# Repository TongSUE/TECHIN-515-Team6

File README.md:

# AuraSync — Context-Aware Scent Diffuser

**AuraSync** automatically detects bathroom context (shower, odor, presence) via sensor fusion and triggers a fragrance diffuser at the right moment — no manual input required.

**Devlog:** [tongsue.github.io/TECHIN-515-Team6](https://tongsue.github.io/TECHIN-515-Team6/)  
**Course:** TECHIN 515 Hardware-Software Lab II, UW, Spring 2026  
**Team:** Yutong Luo (@TongSUE) · Lucia Shen (@xtshen777)

---

## Hardware

| Component | Role |
|---|---|
| Seeed XIAO ESP32-S3 | MCU — dual-core, 8 MB PSRAM, native I2S |
| Adafruit SPH0645LM4H | I2S MEMS microphone — voice recognition |
| HC-SR501 PIR | Presence detection — triggers actuation |
| Adafruit BME680 | Temp / humidity / pressure / VOC (I2C 0x77) |
| Ultrasonic atomizer + 2N2222 NPN | Fragrance mist actuation |
| MT3608 boost converter + 3.7 V LiPo | Power supply |

### Pin Assignments

| Function | Arduino Pin | GPIO |
|---|---|---|
| I2C SDA (BME680) | D4 | 5 |
| I2C SCL (BME680) | D5 | 6 |
| I2S BCLK (SPH0645) | D8 | 7 |
| I2S LRCLK (SPH0645) | D9 | 8 |
| I2S DOUT (SPH0645) | D10 | 9 |
| PIR signal (HC-SR501) | — | 4 |
| Atomizer MOSFET gate | — | 5 |
| Status LED | D0 | 21 |

> SPH0645: SEL pin → GND (left channel). Data in bits [31:14] of 32-bit I2S frame.  
> BME680: use `Wire.begin()` with no arguments — the framework maps D4/D5 by default.

---

## Repository Layout

```
Web/                          ← git root (this repo)
├── Code/
│   ├── AuraSync/             ← main firmware (two-layer state machine)
│   │   ├── AuraSync.ino
│   │   ├── partitions.csv    ← custom flash layout (app0 3.7 MB + model SPIFFS 4.25 MB)
│   │   └── secrets.h.example ← copy to secrets.h and fill in credentials
│   ├── VoiceTest/            ← ESP-SR voice recognition prototype
│   │   └── voice_monitor.html← Web Serial browser monitor
│   ├── FirebaseTest/         ← VoiceTest + Firebase Realtime Database
│   ├── MicTest/              ← SPH0645 bring-up / VAD test
│   ├── PIRTest/              ← PIR motion-triggered spray controller
│   └── PsramTest/            ← PSRAM validation
├── KiCAD/AuraSync_v1/        ← schematic + PCB layout (KiCAD 9)
├── monitor/
│   ├── voice_monitor.py      ← real-time serial monitor (USB, Streamlit)
│   ├── firebase_dashboard.py ← cloud dashboard (reads Firebase, no USB needed)
│   └── requirements.txt
├── web-devlog/               ← React + Vite devlog site
└── README.md
```

---

## Flashing AuraSync (Main Firmware)

1. Copy `Code/AuraSync/secrets.h.example` → `Code/AuraSync/secrets.h` and fill in your WiFi + Firebase credentials
2. Open `Code/AuraSync/AuraSync.ino` in Arduino IDE
3. **Tools → Board:** Seeed XIAO ESP32-S3
4. **Tools → PSRAM:** OPI PSRAM
5. **Tools → Partition Scheme:** Huge APP (3MB No OTA / 1MB SPIFFS)
6. Run `Code/VoiceTest/flash_model.ps1` **once** to write ESP-SR models to flash
7. Upload `AuraSync.ino`
8. Say **"Aura"** to open the 7-second command window, then **"Spray"** or **"Stop"**; PIR presence for ≥ 3 s also triggers spray

---

## Running the Serial Voice Monitor

Streams live audio level and recognised commands from the ESP32-S3 over USB serial.

**Requirements:** Python 3.9+, ESP32-S3 flashed with `VoiceTest.ino` or `AuraSync.ino`, Arduino IDE serial monitor **closed**.

```bash
cd monitor
pip install -r requirements.txt
streamlit run voice_monitor.py
```

Opens at `http://localhost:8501`. The app auto-detects the COM port — no configuration needed.

---

## Running the Firebase Cloud Dashboard

Reads spray events from Firebase Realtime Database — no USB connection required.

```bash
cd monitor
pip install -r requirements.txt
streamlit run firebase_dashboard.py
```

Opens at `http://localhost:8502`. Supports dark/light mode toggle; auto-refreshes every 5 seconds.

---

## Flashing VoiceTest (Voice Recognition Prototype)

1. Open `Code/VoiceTest/VoiceTest.ino` in Arduino IDE
2. **Tools → Board:** Seeed XIAO ESP32-S3
3. **Tools → PSRAM:** OPI PSRAM
4. **Tools → Partition Scheme:** Huge APP (3MB No OTA / 1MB SPIFFS)
5. Run `Code/VoiceTest/flash_model.ps1` **once** to write ESP-SR models to flash
6. Upload `VoiceTest.ino`
7. Say **"Aura"** to open the 7-second command window, then **"Spray"** or **"Stop"**

---

## Firmware Overview

### `Code/AuraSync/AuraSync.ino` — Main firmware (Week 4+)

Two-layer state machine, non-blocking (`millis()` only, no `delay()` in main loop):

**Layer 1 — System Mode** (PIR-driven presence):
```
MODE_SLEEP  ──PIR detected──▶  MODE_AWAKE
MODE_AWAKE  ──60 s no PIR──▶  MODE_SLEEP
```

**Layer 2 — Spray State** (shared absolute cooldown):
```
SPRAY_IDLE → SPRAY_SPRAYING (5 s) → SPRAY_COOLDOWN (20 s test / 3 min prod) → SPRAY_IDLE
```

Four-priority trigger model: P1 voice/app (bypasses cooldown, works in SLEEP) → P2 extreme VOC < 10 kΩ (works in SLEEP, queues during cooldown) → P3 PIR + VOC inflection (AWAKE + IDLE only).

FreeRTOS dual-core: I2S + ESP-SR on Core 1 at max priority; PIR, state machine, Firebase, BME680 on Core 0. Power saving: `WiFi.setSleep(WIFI_PS_MAX_MODEM)` + Core 0 throttle in SLEEP mode (~30 mA idle from 2000 mAh LiPo ≈ 60–70 h).

### `Code/VoiceTest/VoiceTest.ino` — Voice recognition prototype

ESP-SR AFE + MultiNet v7 on FreeRTOS Core 1. Wake-word state machine:

```
IDLE → (say "Aura") → LISTENING [7 s] → (say "Spray"/"Stop") → IDLE
```

### `Code/FirebaseTest/FirebaseTest.ino` — Voice + Firebase

Extends VoiceTest: SR task (Core 1) → FreeRTOS queue → `loop()` (Core 0) → `Firebase.RTDB.pushJSON()`. Auth via database-secret legacy token; NTP time sync at boot.

---

## Devlog Site

Built with React 19 + Vite. Auto-deployed to GitHub Pages.

```bash
cd web-devlog
npm install
npm run dev       # local preview
npm run build     # production build
```

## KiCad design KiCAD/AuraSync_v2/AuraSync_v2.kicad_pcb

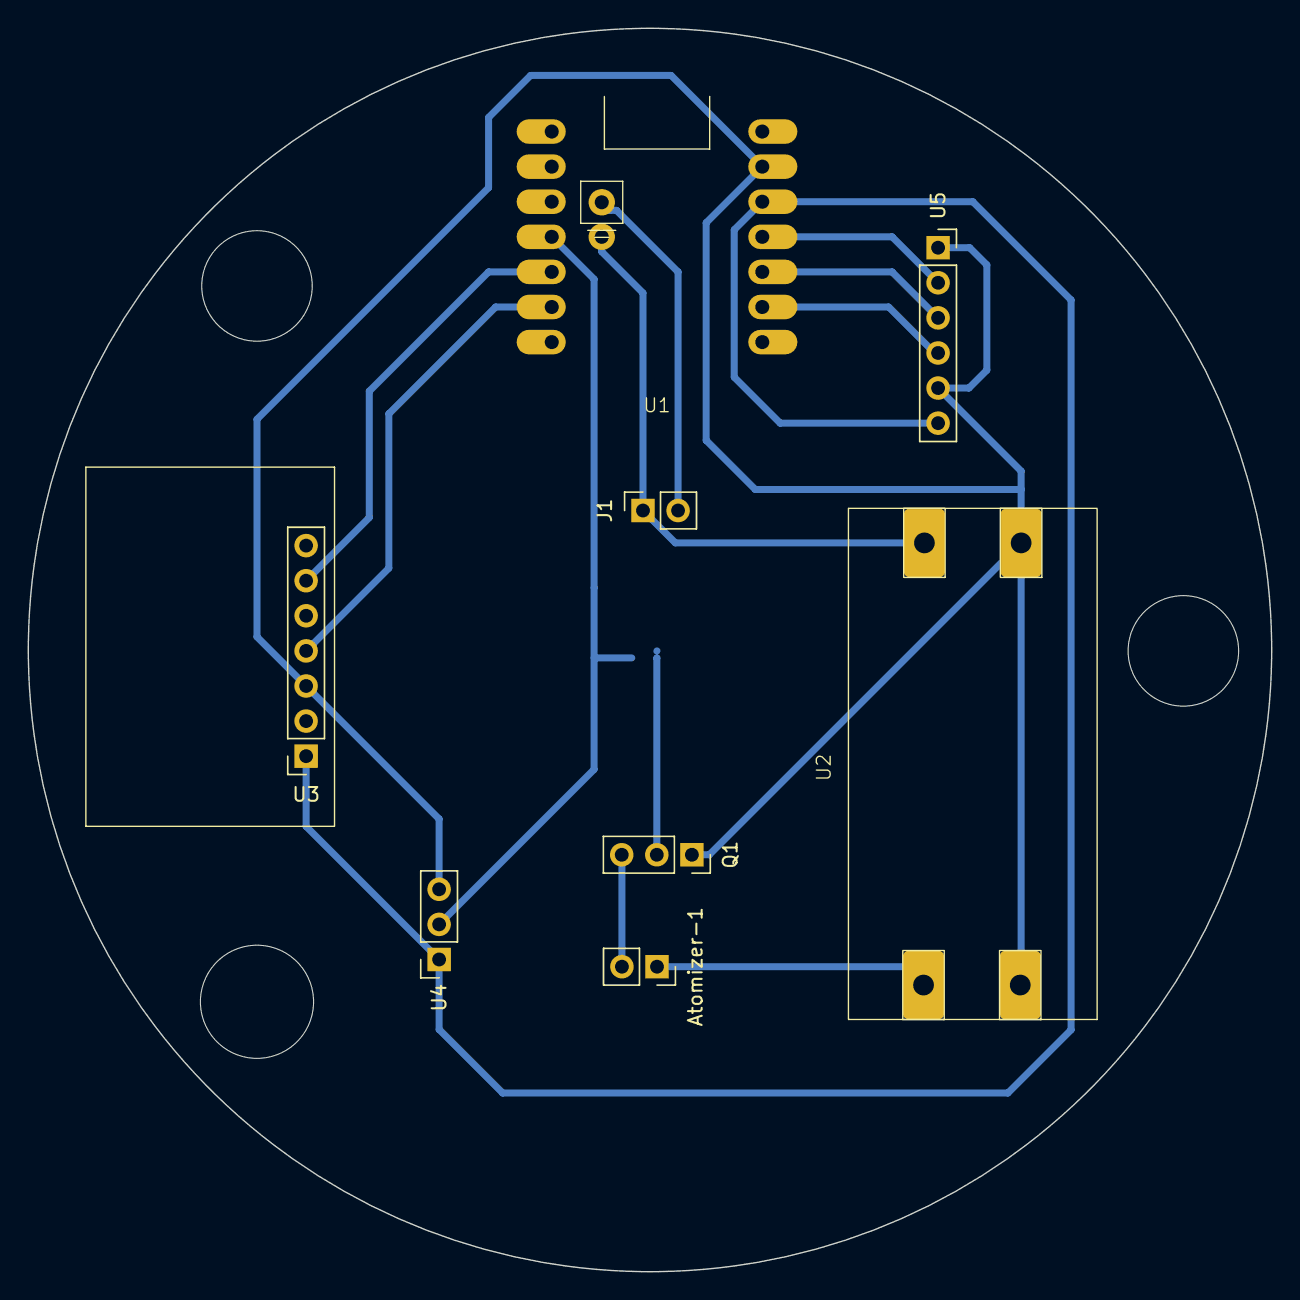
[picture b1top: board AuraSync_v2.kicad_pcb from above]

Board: 2 copper layers, 90.0 x 90.0 mm, 9 parts (1 on the bottom side), 13 nets.

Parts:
Atomizer-1: Atomizer; PinSocket_1x02_P2.54mm_Vertical
J1: Battery; PinSocket_1x02_P2.54mm_Vertical
Q1: 2N2222; PinSocket_1x03_P2.54mm_Vertical
R1: 1k; R_0603_1608Metric_Pad0.98x0.95mm_HandSolder
U1: ESP32S3; XIAO_ESP32
U2: MT3608
U3: BME680; PinSocket_1x07_P2.54mm_Vertical
U4: HC-SR501PIR; PinSocket_1x03_P2.54mm_Vertical
U5: SPH0645_Mic; PinSocket_1x06_P2.54mm_Vertical

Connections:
+3.3V: U1.12 (3V3), U3.1 (VIN), U4.1 (VCC), U5.6 (3V)
+5V: Atomizer-1.1, U2.1 (VOUT+)
/BATT+: J1.1, U1.15 (+BATT), U2.3 (VIN+)
/BATT-: J1.2, U1.16 (-BATT)
/BLCK: U1.9 (GPIO7_A8_D8_SCK), U5.4 (BLCK)
/DOUT: U1.11 (GPIO9_A10_D10_MOSI), U5.2 (DOUT)
/LRCL: U1.10 (GPIO8_A9_D9_MISO), U5.3 (LRCL)
/SCL: U1.6 (GPIO6_A5_D5_SCL), U3.4 (SCK)
/SDA: U1.5 (GPIO5_A4_D4_SDA), U3.6 (SDI)
/Signal: R1.2, U1.4 (GPIO4_A3_D3), U4.2 (OUT)
GND: Q1.1 (E), U1.13 (GND), U2.2 (VOUT-), U2.4 (VIN-), U3.3 (GND), U4.3 (GND), U5.1 (SEL), U5.5 (GND)
unnamed: Atomizer-1.2, Q1.3 (C)
unnamed: Q1.2 (B), R1.1

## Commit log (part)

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2026-04-07 Add TEAM6 devlog SPA, GitHub Pages workflow, and week 1 architecture figure in Markdown.
    Made-with: Cursor
2026-04-07 Add GitHub Actions workflow for GitHub Pages deployment
    This workflow automates the deployment of static content to GitHub Pages upon pushes to the main branch or manual triggers.
2026-04-07 feat(web-devlog): KaTeX math, UX polish, week-01 content, GitHub repo URL
    - Add remark-math and rehype-katex with single-dollar math disabled so BOM
    prices stay literal; use \\(...\\) for inline and ... for display math.
    - Import KaTeX CSS; tune markdown-doc styles for dark mode.
    - Fix week-01 gradients and arrows; embed medium-fidelity user flow diagram.
    - Point devlog githubRepo to TECHIN-515-Team6.
    Made-with: Cursor
2026-04-07 feat(web-devlog): AuraSync devlog UI, week-01 content, carryover tasks, user flow diagram
    - Homepage hero, vision, timeline, team copy and motion polish
    - Week 1 markdown: structure, planned_next, HTML user flow diagram embed
    - Prior-week checklist on timeline and week pages via prior_week_progress
    - GitHub repo URL, TOC bookends (Opening / Main / Closing)
    - lucide icons, cursor aura, route transitions, rehype-raw for embeds
    Made-with: Cursor
2026-04-07 fix(pages): remove conflicting static Pages workflow
    static.yml uploaded the whole repo root to GitHub Pages, which has no
    Vite build output and overwrote/raced deploy-pages.yml. Only
    deploy-pages.yml should publish web-devlog/dist with VITE_BASE_PATH.
    Made-with: Cursor
2026-04-20 update code for pir and atomizer test code
2026-04-30 chore: tidy gitignore whitespace
2026-05-02 feat: add CLAUDE.md context, requirements.txt, and updated firmware/scripts
2026-05-10 backup: save AuraSync v3 original before ML deployment
2026-05-10 feat(firmware): deploy IAQ MLP + Shower CNN into AuraSync via BSEC2 + ring buffer
